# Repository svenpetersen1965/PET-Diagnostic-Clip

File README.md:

# PET-Diagnostic-Clip
This is a modern remake of the two Commodore Diagnostic Clips

<br>Complete Diagnostic Clip Set

<br>Diagnostic Clip installed in a CBM3016 (non CRTC machine)

<br>Diagnostic Clip installed in a CBM8032 (CRTC machine)

# PET Diagnostic Software (40 column, non CRTC):<br>
<br>Opening Screen

<br>Actual tests

<br>Actual tests (continued)

# PET Diagnostic Software (80 column, CRTC):<br>
<br>Opening Screen

<br>Actual tests

# Binaries for the EPROM
The name of the combined file is "80colCRCTv1.1_40colCRCTv2.0_diag3202350g_diag320350g.bin". It contains:
<table>
  <thead>
    <tr>
      <th>EPROM Offset</th><th>Software</th><th>DIP Switch</th>
    </tr>
  </thead>
  <tbody>
    <tr>
      <td>$0000</td><td>80_col_diagnostic_v1.1.bin</td><td>A[15..12]: 0000 =  ON  ON  ON  ON</td>
    </tr>
    <tr>
      <td>$1000</td><td>40_col_diagnostic_v2.0.bin</td><td>A[15..12]: 0001 =  ON  ON  ON  OFF</td>
    </tr>
    <tr>
      <td>$2000</td><td>901447-30_diagnostic_320350g_$9000.bin</td><td>A[15..12]: 0010 =  ON  ON  OFF ON</td>
    </tr>
    <tr>
      <td>$3000</td><td>901447-30_diagnostic_320350g_$9000.bin</td><td>A[15..12]: 0011 =  ON  ON  OFF OFF</td>
    </tr>
 </tbody>
</table>    
    
The Diagnostic 320350g is double. The reason is, the computer would crash if an empty slot is selected. So all slots, that can be selected with the two low switches of the dip switch are occupied.

In a subdirectory, there are some "PETtester" Softwares. These are not a complete test. The (vice) screen shots are included. It could also be installed on the clip, if desired. 
# CBM8296
This part of the project is not tested yet. <b>The release is preliminary</b>.

<br>CBM8296 Diagnostic Harness (complete)

The diagnostic software for the CBM8296 is contained in the respective folder. There is also a merged binary file ("80colCRCTv1.1_40colCRCTv2.0_diag3202350g_diag320350g_8296.bin") which contains the 324806-01.bin at offset address $4000 (A[15..12]: 0100 =  ON  OFF  ON ON).

<b>State of testing:</b><br>
14.06.2023:<br>
* all dongles work with the original (Commodore) clip
* the cassette dongle case reqires modification
21.06.2023:<br>
The CBM8296 can actively switch the /NOROM signal (register @$FFF0). It does so to access the RAM underneath the ROMs. As a result, the diagnostic ROM in the clip is getting visible, which interferes with the test of the upper RAM banks.

A solution is switching off the /NOROM signal in the clip by using the 2nd stage of the external switch. The /NOROM trace at J1, pin 9 has to be cut open and connected to the middle pin of the said switch, the right pin ("active" position) has to be connected to the clip's internal /NOROM signal, e.g. at SW4.  

<br>/NOROM modification of Clip Rev. 2

The clip Rev. 3 incorporates this modificaltion. Since I do not own a CBM8296, I cannot test the new clip with this computer. 

# Additional Information
I have held a presentation about this topic for Commodore Users Europe on Sept. 23rd, 2023. The pdf of the power point presentation can be found here: <a href="https://github.com/svenpetersen1965/PET-Diagnostic-Clip/commit/a3cc22ed0ae75f65ffd660c29feb877c46cf6521">here</a>

Also check my website for <a href="http://tech.guitarsite.de/petcbm_diag_clip.html">additional information</a>.

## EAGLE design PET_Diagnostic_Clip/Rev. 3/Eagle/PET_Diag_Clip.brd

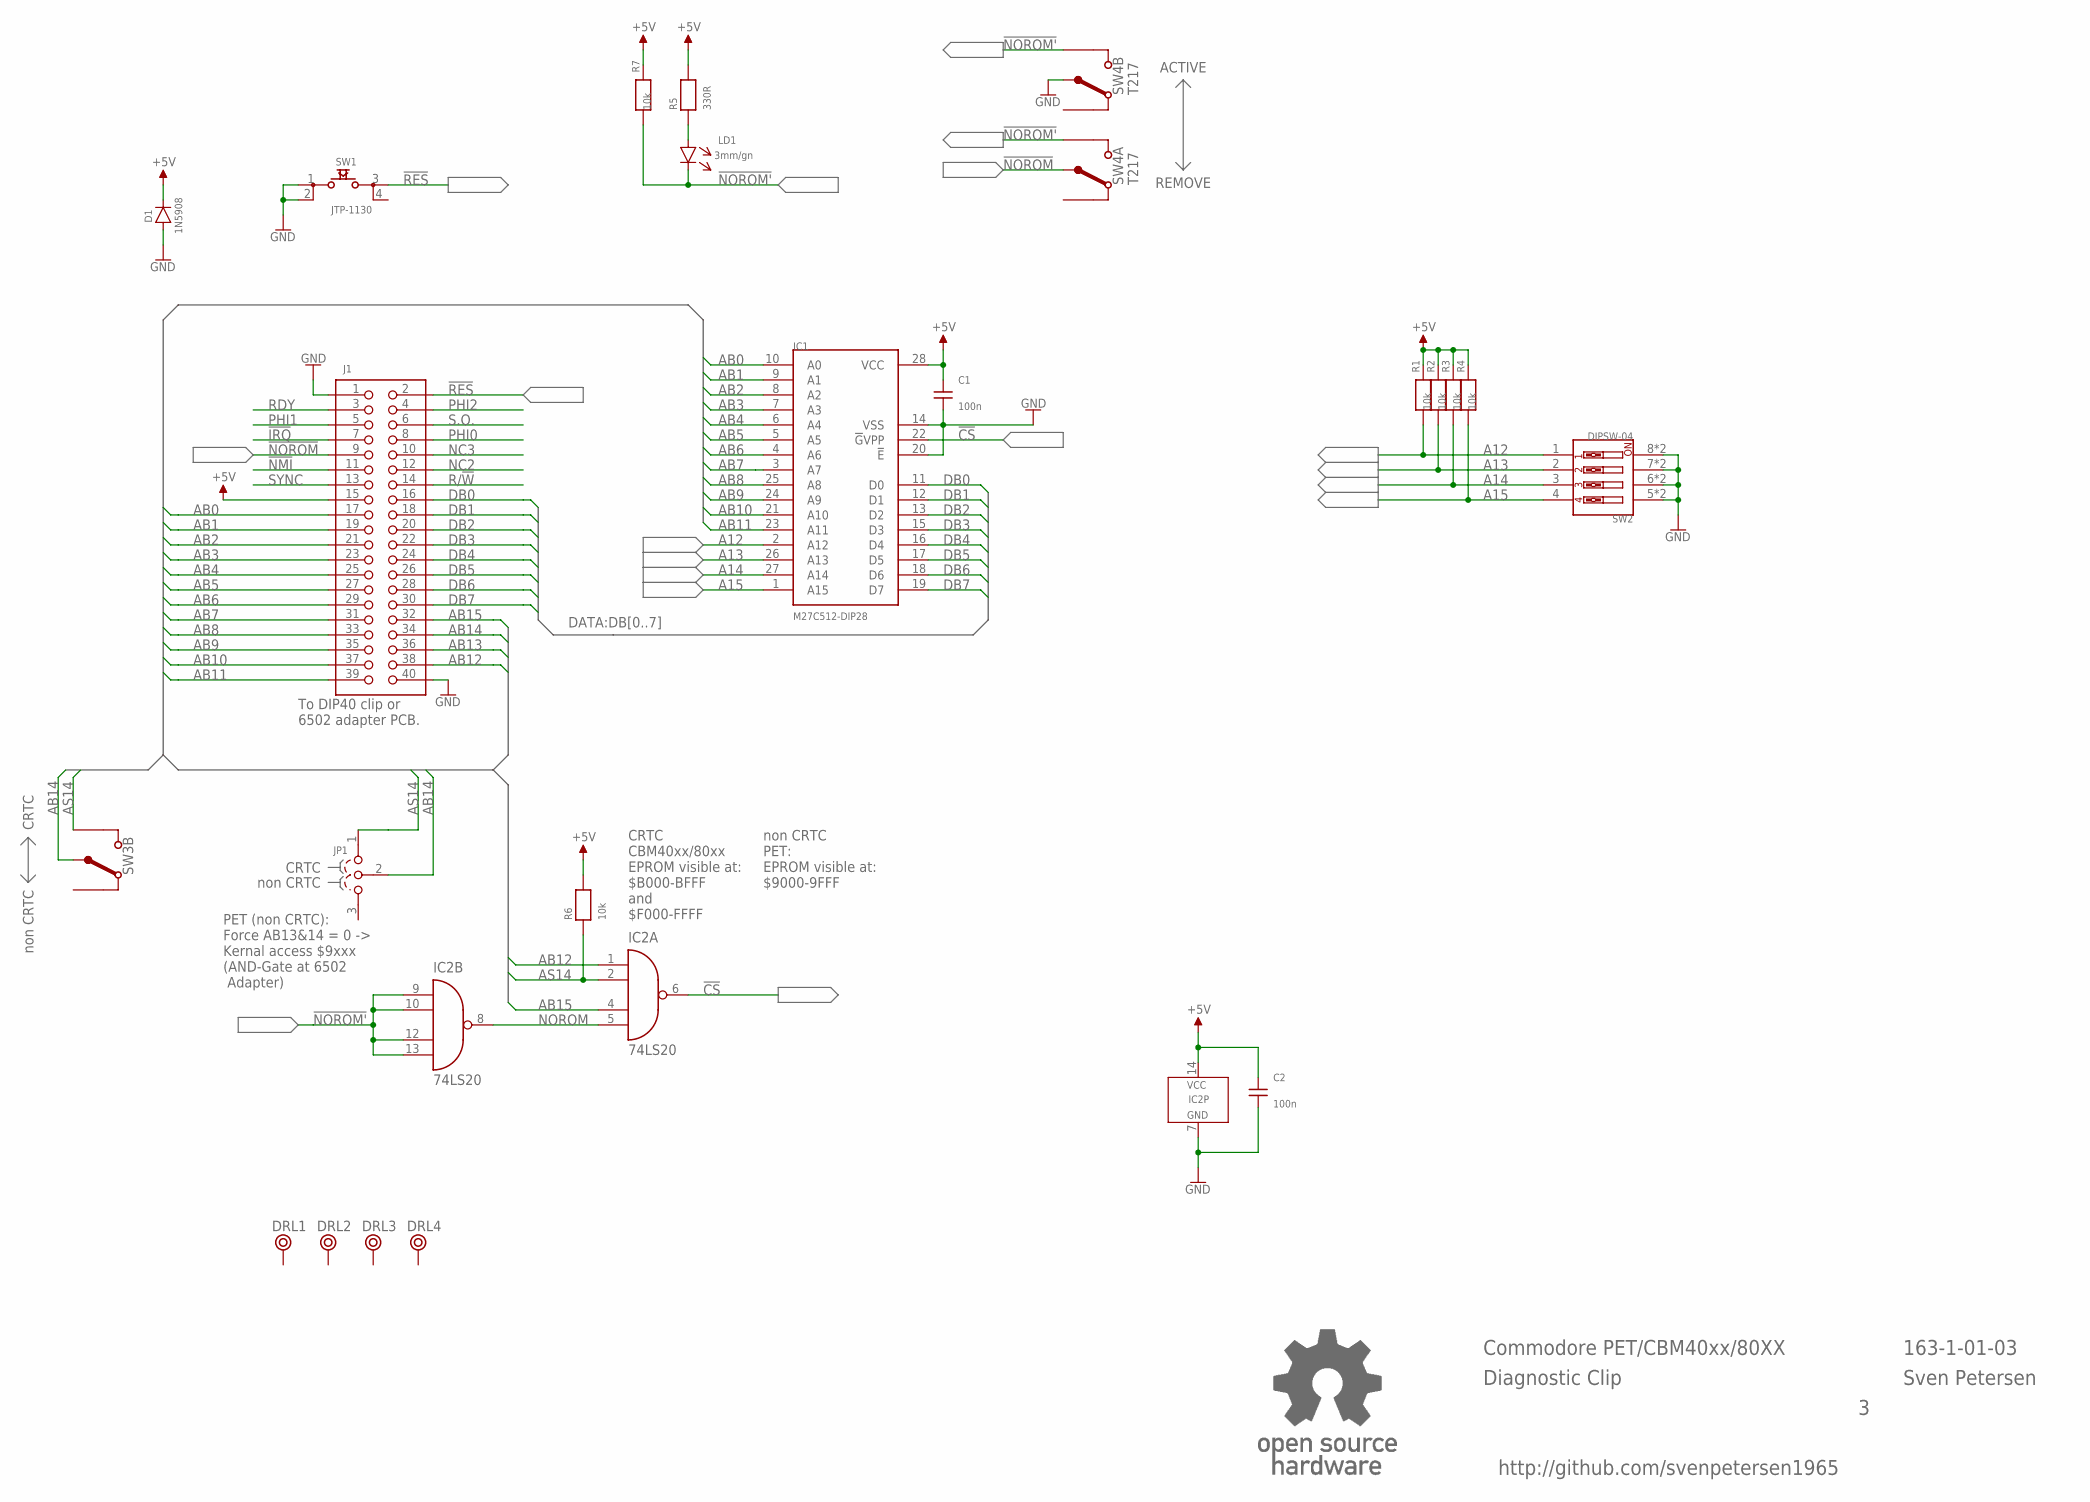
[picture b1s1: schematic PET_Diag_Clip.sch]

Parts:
C1, C2: 100n; C-2,5
D1: 1N5908; DO-201
DRL1, DRL2, DRL3, DRL4: BOHR3,5
IC1: M27C512-DIP28; DIL28-6
IC2: 74LS20; DIL-14
J1: PINHD-2X20WV; 2X20WV
JP1: COMBI-3P
LD1: 3mm/gn; 3MM
R1, R2, R3, R4, R6, R7: 10k; R-10
R5: 330R; R-10
SW1: JTP-1130
SW2: DIPSW-04; DIPSW-04V-COMBI
SW3: MSS22D18; DPDT_9MM
SW4: T217; T217_SIDE
U$13: OPEN_SOURCE_HW; OPENHW

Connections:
!CS: IC1.22 (!G!VPP), IC2.6 (O)
!IRQ: J1.7
!NMI: J1.11
!NOROM: J1.9, SW4.COM1 (COM)
!NOROM': IC2.9 (I0), IC2.10 (I1), IC2.12 (I2), IC2.13 (I3), LD1.C (K), R7.2, SW4.UP1 (UP), SW4.UP2 (UP)
!RES: J1.2, SW1.3
+5V: C1.2, C2.2, D1.K, IC1.28 (VCC), IC2.14 (VCC), J1.15, R1.1, R2.1, R3.1, R4.1, R5.2, R6.2, R7.1
A12: IC1.2 (A12), R1.2, SW2.1
A13: IC1.26 (A13), R2.2, SW2.2
A14: IC1.27 (A14), R3.2, SW2.3
A15: IC1.1 (A15), R4.2, SW2.4
AB0: IC1.10 (A0), J1.17
AB1: IC1.9 (A1), J1.19
AB2: IC1.8 (A2), J1.21
AB3: IC1.7 (A3), J1.23
AB4: IC1.6 (A4), J1.25
AB5: IC1.5 (A5), J1.27
AB6: IC1.4 (A6), J1.29
AB7: IC1.3 (A7), J1.31
AB8: IC1.25 (A8), J1.33
AB9: IC1.24 (A9), J1.35
AB10: IC1.21 (A10), J1.37
AB11: IC1.23 (A11), J1.39
AB12: IC2.1 (I0), J1.38
AB13: J1.36
AB14: J1.34, JP1.2, SW3.5 (COM)
AB15: IC2.4 (I2), J1.32
AS14: IC2.2 (I1), JP1.1, R6.1, SW3.6 (UP)
DB0: IC1.11 (D0), J1.16
DB1: IC1.12 (D1), J1.18
DB2: IC1.13 (D2), J1.20
DB3: IC1.15 (D3), J1.22
DB4: IC1.16 (D4), J1.24
DB5: IC1.17 (D5), J1.26
DB6: IC1.18 (D6), J1.28
DB7: IC1.19 (D7), J1.30
GND: C1.1, C2.1, D1.A, IC1.14 (VSS), IC1.20 (!E), IC2.7 (GND), J1.1, J1.40, SW1.1, SW1.2, SW2.5, SW2.5A (5), SW2.6, SW2.6A (6), SW2.7, SW2.7A (7), SW2.8, SW2.8A (8), SW4.COM2 (COM)
unnamed: LD1.A, R5.1
NC2: J1.12
NC3: J1.10
NOROM: IC2.5 (I3), IC2.8 (O)
PHI0: J1.8
PHI1: J1.5
PHI2: J1.4
R/!W: J1.14
RDY: J1.3
S.O.: J1.6
SYNC: J1.13

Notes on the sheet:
Commodore PET/CBM40xx/80XX
Diagnostic Clip
Sven Petersen
163-1-01-03
http://github.com/svenpetersen1965
To DIP40 clip or 6502 adapter PCB.
CRTC CBM40xx/80xx EPROM visible at: $B000-BFFF and $F000-FFFF
CRTC
non CRTC
PET (non CRTC): Force AB13&14 = 0 -> Kernal access $9xxx (AND-Gate at 6502 Adapter)
non CRTC PET: EPROM visible at: $9000-9FFF
ACTIVE
REMOVE

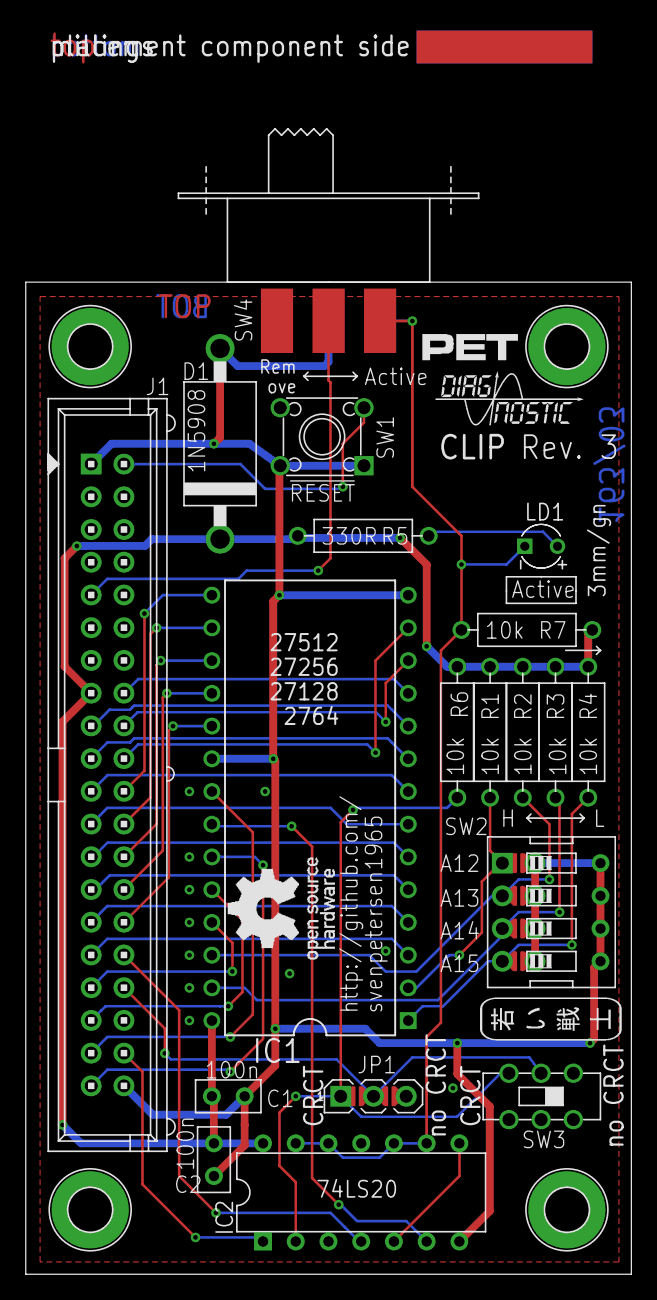
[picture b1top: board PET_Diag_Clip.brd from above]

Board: 2 copper layers, 47.0 x 77.0 mm, 29 parts (0 on the bottom side), 36 nets.

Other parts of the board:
U$27: PET_SMALL
U$30: DIAG_SMALL
U$34: 2LAYER
U$35: PCB-TITLE/
U$42: SVEN_TAG

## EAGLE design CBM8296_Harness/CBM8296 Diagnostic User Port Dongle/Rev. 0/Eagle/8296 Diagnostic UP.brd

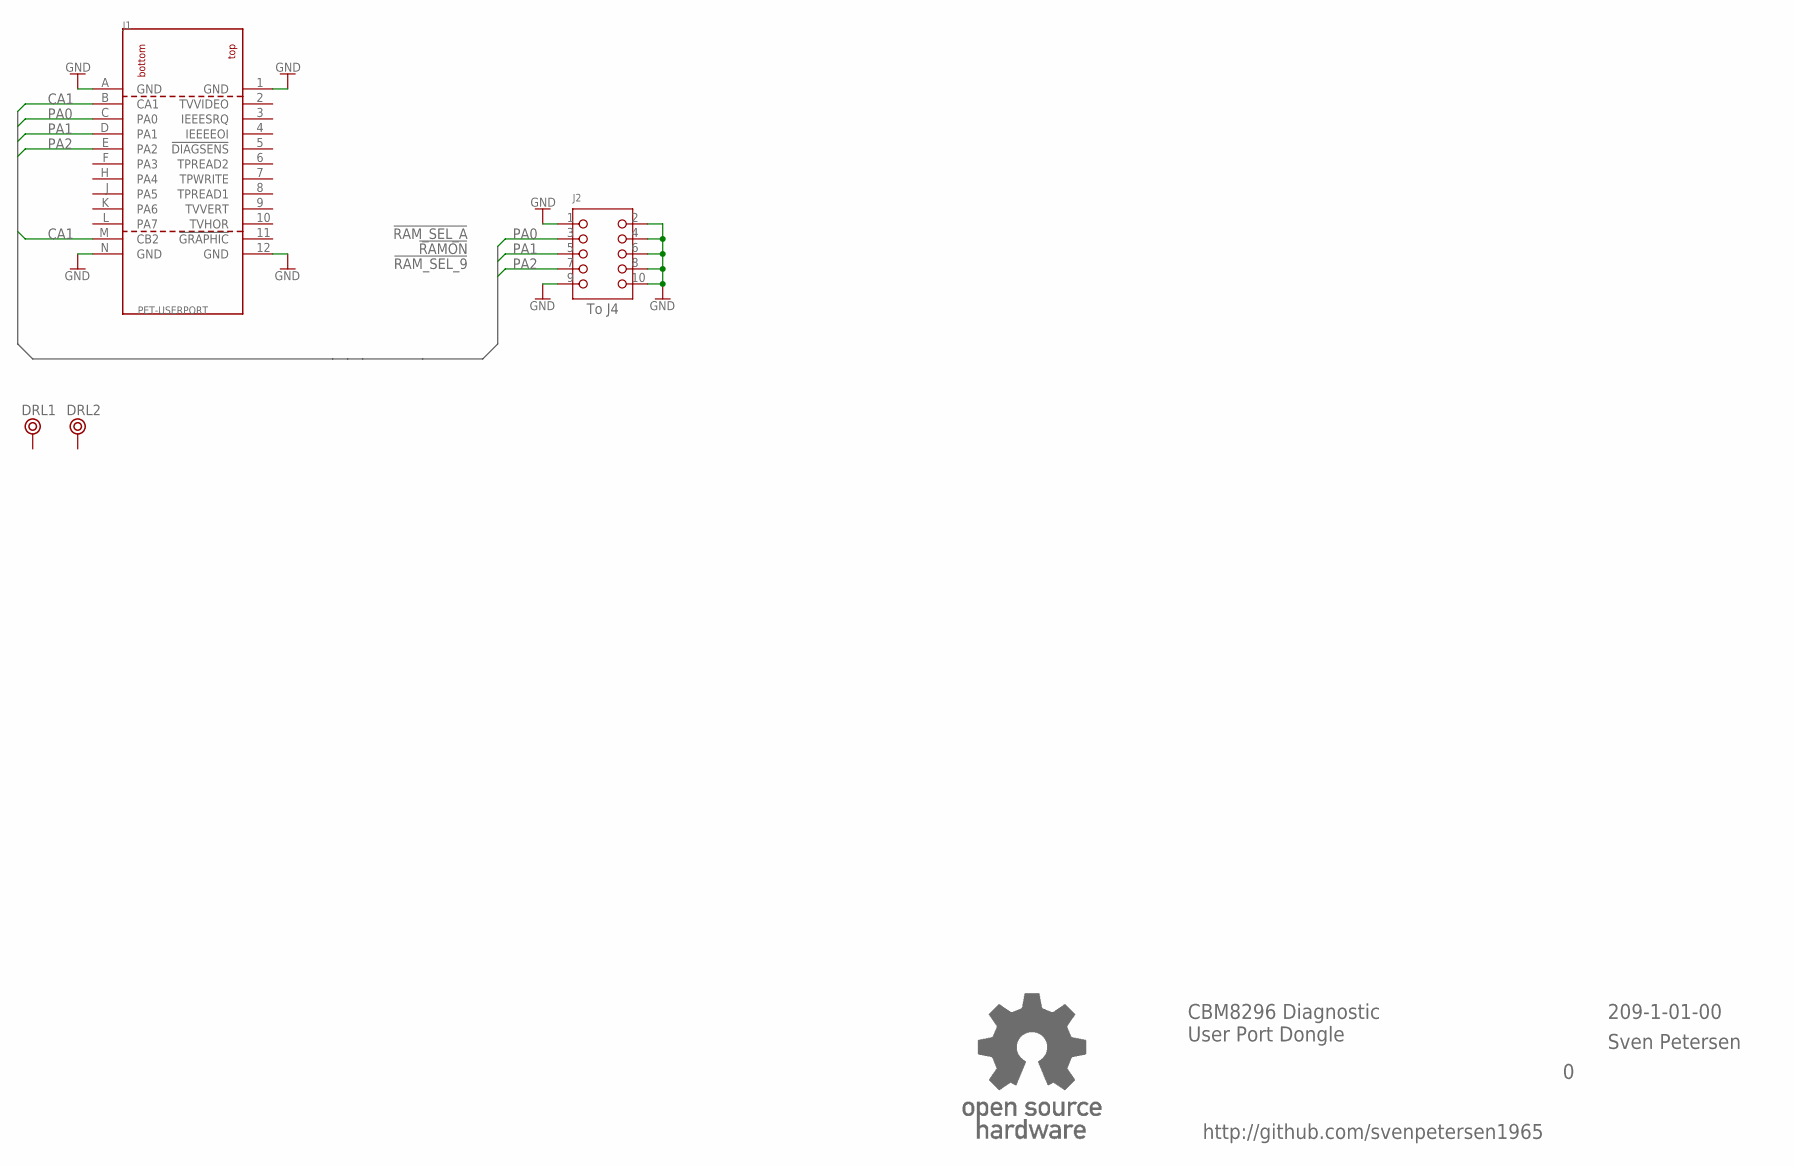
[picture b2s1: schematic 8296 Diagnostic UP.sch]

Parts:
DRL1, DRL2: BOHR3,5
J1: PET-USERPORT; USERPORT
J2: 2X05WV
U$13: OPEN_SOURCE_HW; OPENHW

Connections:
CA1: J1.B (CA1), J1.M (CB2)
GND: J1.1 (GND), J1.12 (GND), J1.A (GND), J1.N (GND), J2.1, J2.2, J2.4, J2.6, J2.8, J2.9, J2.10
PA0: J1.C (PA0), J2.3
PA1: J1.D (PA1), J2.5
PA2: J1.E (PA2), J2.7

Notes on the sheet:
CBM8296 Diagnostic User Port Dongle
209-1-01-00
Sven Petersen
http://github.com/svenpetersen1965
To J4
!RAM_SEL_A
!RAMON
!RAM_SEL_9

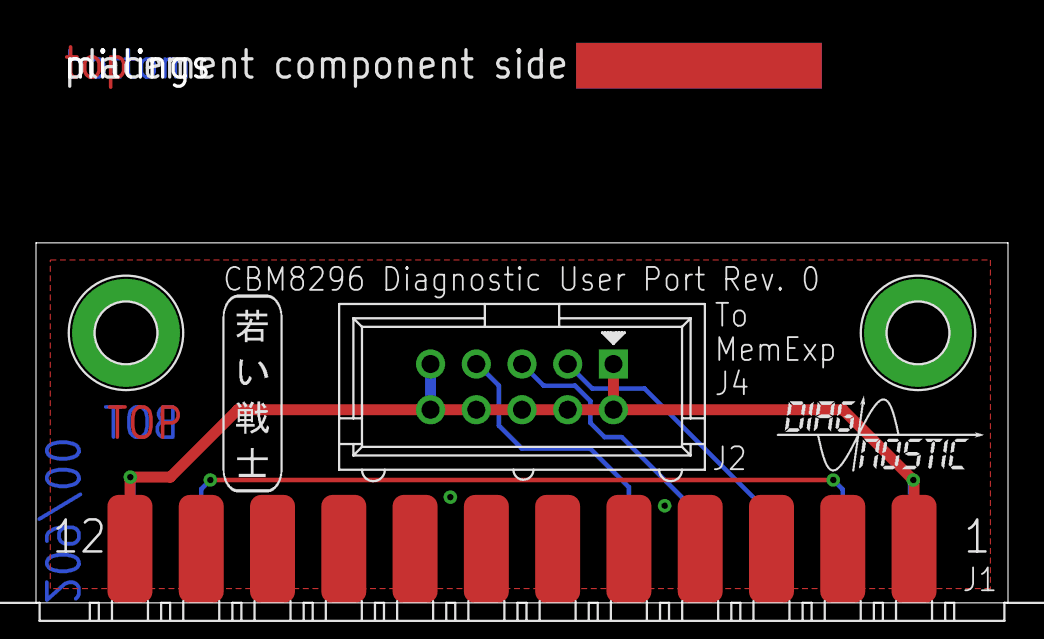
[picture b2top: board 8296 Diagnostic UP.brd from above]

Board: 2 copper layers, 54.0 x 20.0 mm, 9 parts (1 on the bottom side), 5 nets.

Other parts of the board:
U$8: 2LAYER
U$9: PCB-TITLE/
U$10: SVEN_TAG
U$12: DIAG_SMALL

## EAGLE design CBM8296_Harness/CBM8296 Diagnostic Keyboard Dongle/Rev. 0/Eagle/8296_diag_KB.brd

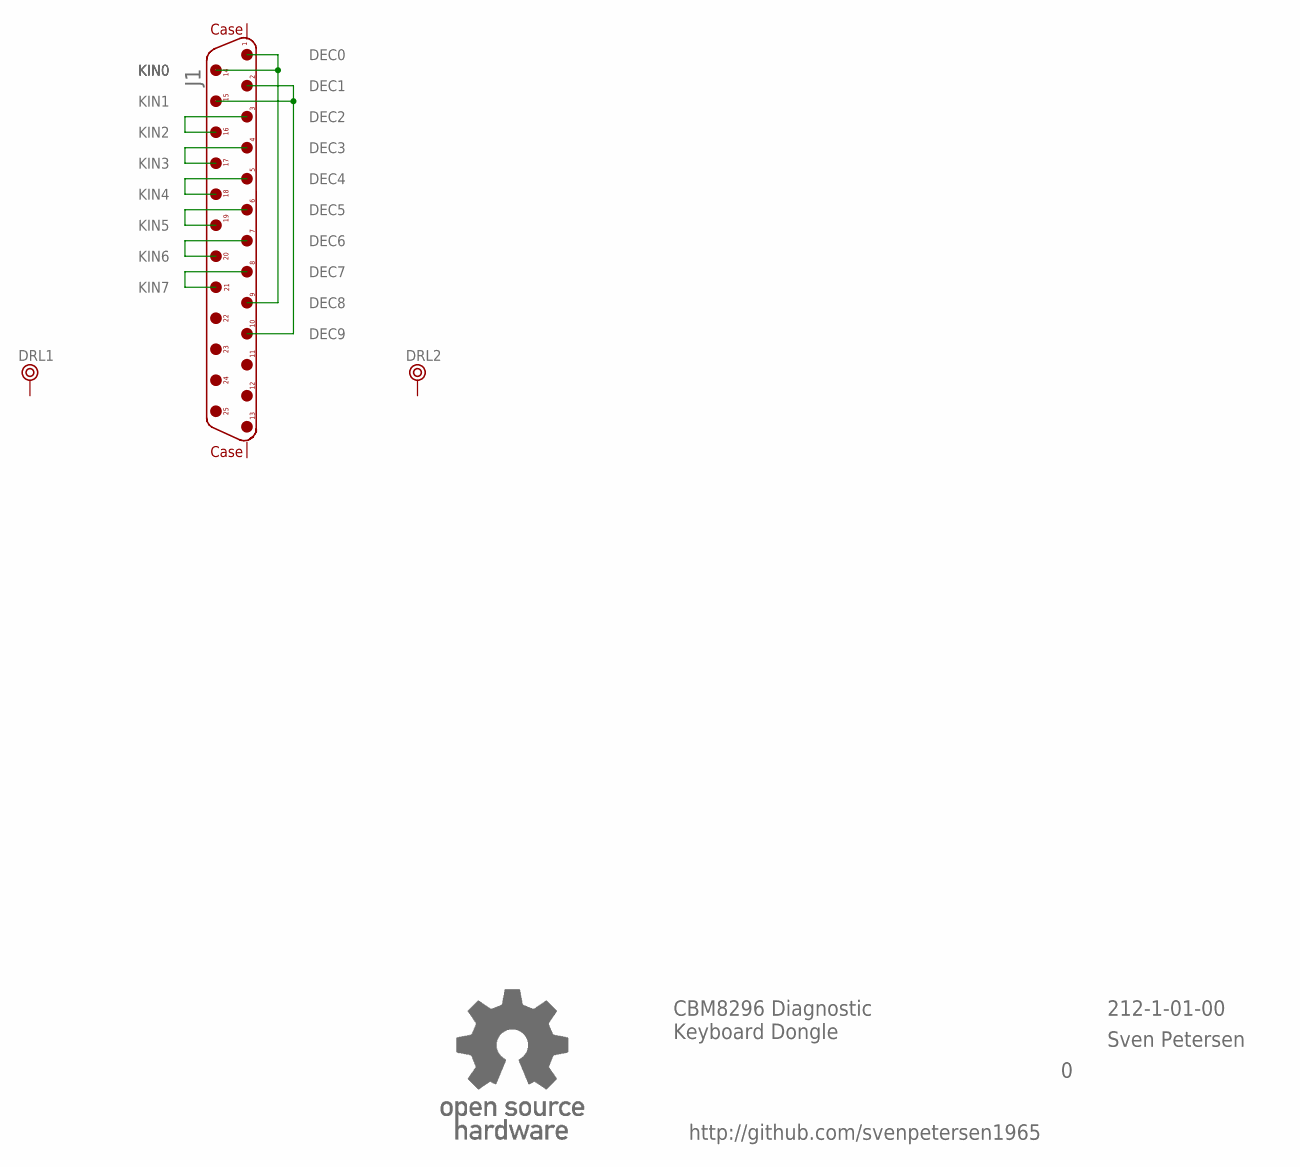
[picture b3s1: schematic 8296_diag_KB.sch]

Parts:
DRL1, DRL2: BOHR3,5
J1: D25M90CLEU
U$13: OPEN_SOURCE_HW; OPENHW

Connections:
unnamed: J1.1, J1.9, J1.14
unnamed: J1.2, J1.10, J1.15
unnamed: J1.3, J1.16
unnamed: J1.4, J1.17
unnamed: J1.5, J1.18
unnamed: J1.6, J1.19
unnamed: J1.7, J1.20
unnamed: J1.8, J1.21

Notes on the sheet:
CBM8296 Diagnostic Keyboard Dongle
212-1-01-00
Sven Petersen
http://github.com/svenpetersen1965
DEC0
DEC1
DEC2
DEC3
DEC4
DEC6
DEC5
DEC7
DEC8
DEC9
KIN0
KIN1
KIN2
KIN3
KIN4
KIN5
KIN6
KIN7

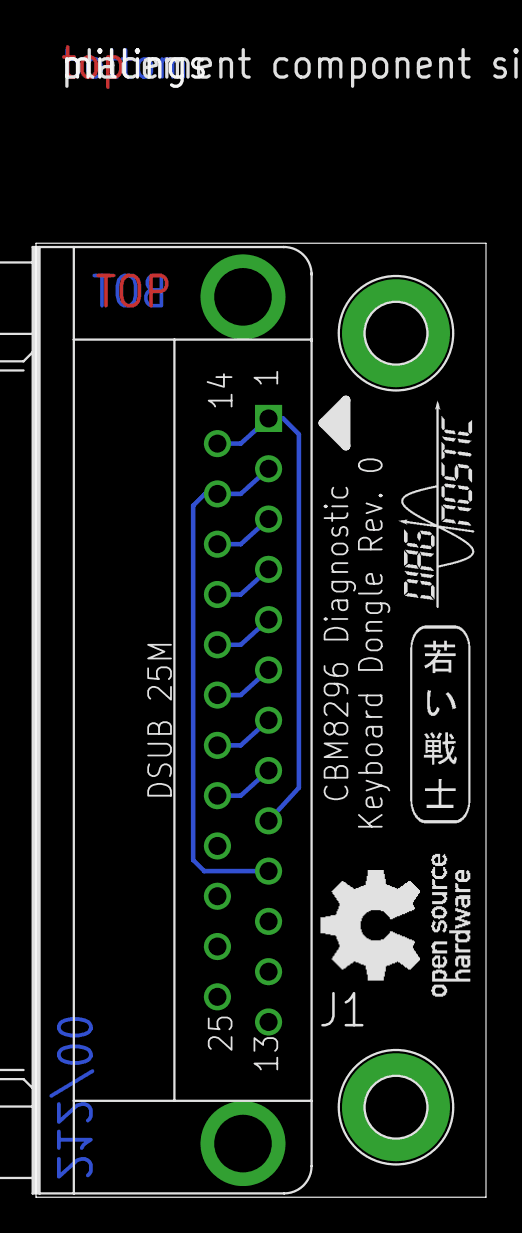
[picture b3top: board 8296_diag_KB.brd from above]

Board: 2 copper layers, 25.0 x 53.0 mm, 8 parts (0 on the bottom side), 8 nets.

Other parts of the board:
U$2: DIAG_SMALL
U$3: SVEN_TAG
U$4: 2LAYER
U$5: PCB-TITLE/

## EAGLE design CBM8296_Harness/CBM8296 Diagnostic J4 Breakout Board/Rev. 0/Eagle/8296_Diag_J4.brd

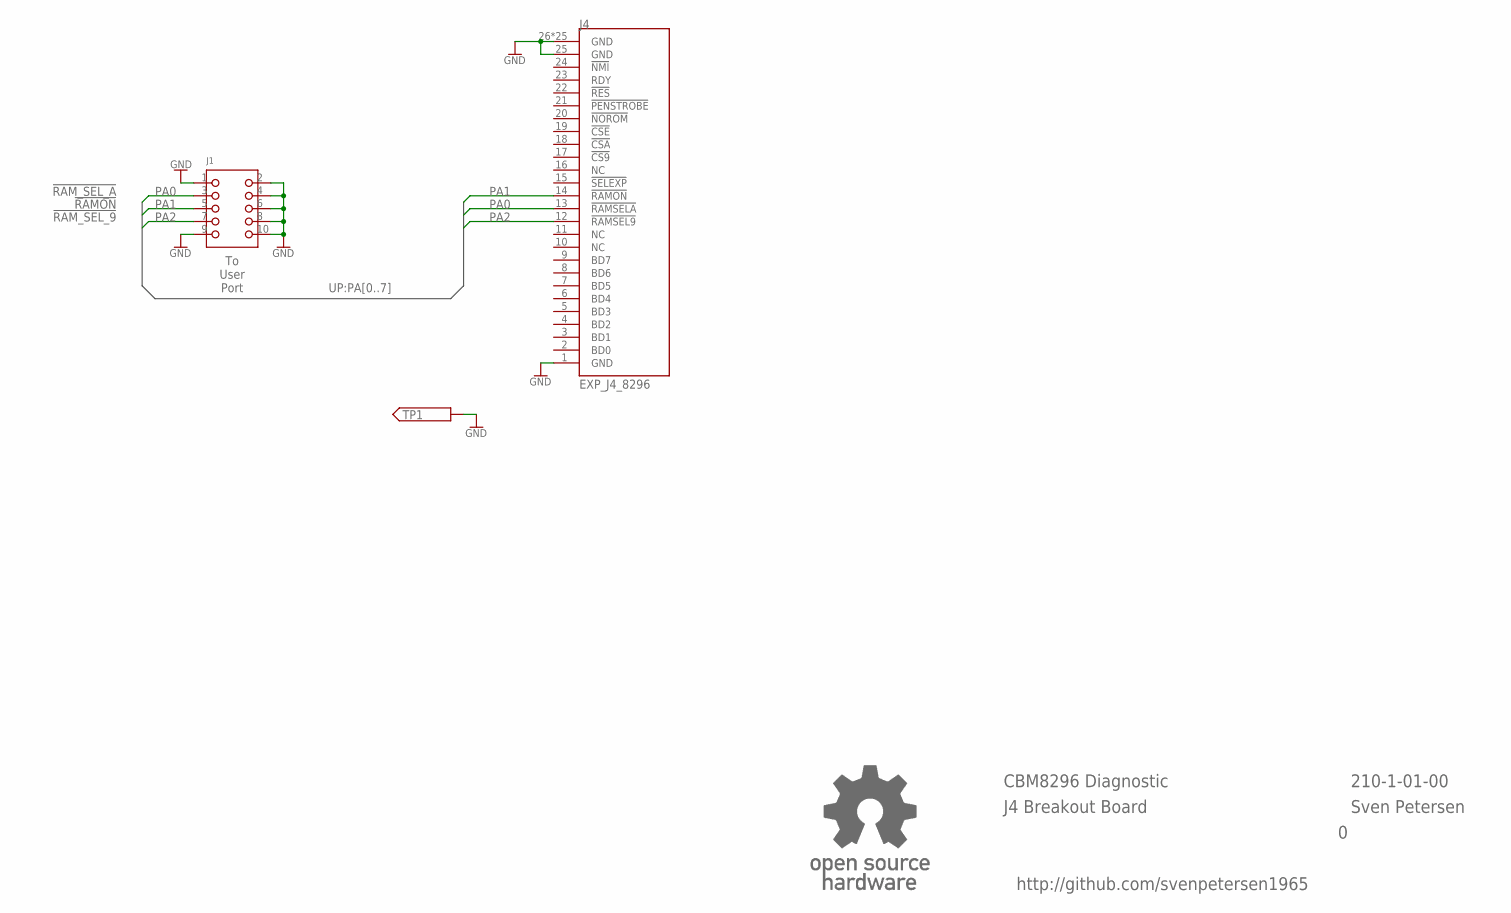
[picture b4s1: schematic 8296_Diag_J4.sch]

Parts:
J1: 2X05WV
J4: EXP_J4_8296; PET_EXPANSION_BOT
TP1: PINHD-1X1; 1X01
U$5: OPEN_SOURCE_HW; OPENHW

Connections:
GND: J1.1, J1.2, J1.4, J1.6, J1.8, J1.9, J1.10, J4.1 (GND), J4.25 (GND), J4.26 (GND), J4.27 (GND), J4.28 (GND), J4.29 (GND), J4.30 (GND), J4.31 (GND), J4.32 (GND), J4.33 (GND), J4.34 (GND), J4.35 (GND), J4.36 (GND), J4.37 (GND), J4.38 (GND), J4.39 (GND), J4.40 (GND), J4.41 (GND), J4.42 (GND), J4.43 (GND), J4.44 (GND), J4.45 (GND), J4.46 (GND), J4.47 (GND), J4.48 (GND), J4.49 (GND), J4.50 (GND), TP1.1
PA0: J1.3, J4.13 (!RAMSELA)
PA1: J1.5, J4.14 (!RAMON)
PA2: J1.7, J4.12 (!RAMSEL9)

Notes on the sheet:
CBM8296 Diagnostic
J4 Breakout Board
210-1-01-00
Sven Petersen
http://github.com/svenpetersen1965
To User Port
!RAM_SEL_A
!RAMON
!RAM_SEL_9

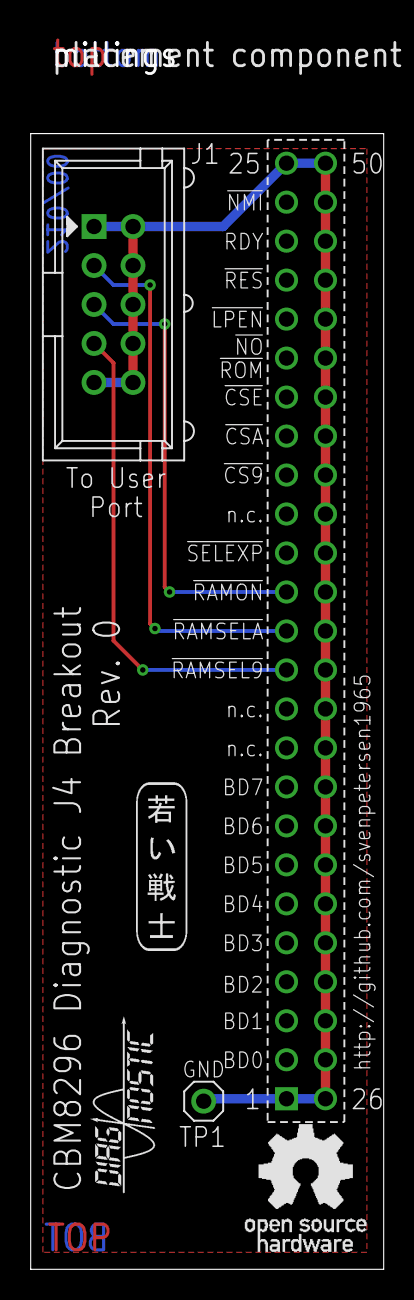
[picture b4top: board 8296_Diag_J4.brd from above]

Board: 2 copper layers, 23.0 x 74.0 mm, 8 parts (0 on the bottom side), 4 nets.

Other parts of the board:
U$8: 2LAYER
U$9: SVEN_TAG
U$10: PCB-TITLE/
U$12: DIAG_SMALL

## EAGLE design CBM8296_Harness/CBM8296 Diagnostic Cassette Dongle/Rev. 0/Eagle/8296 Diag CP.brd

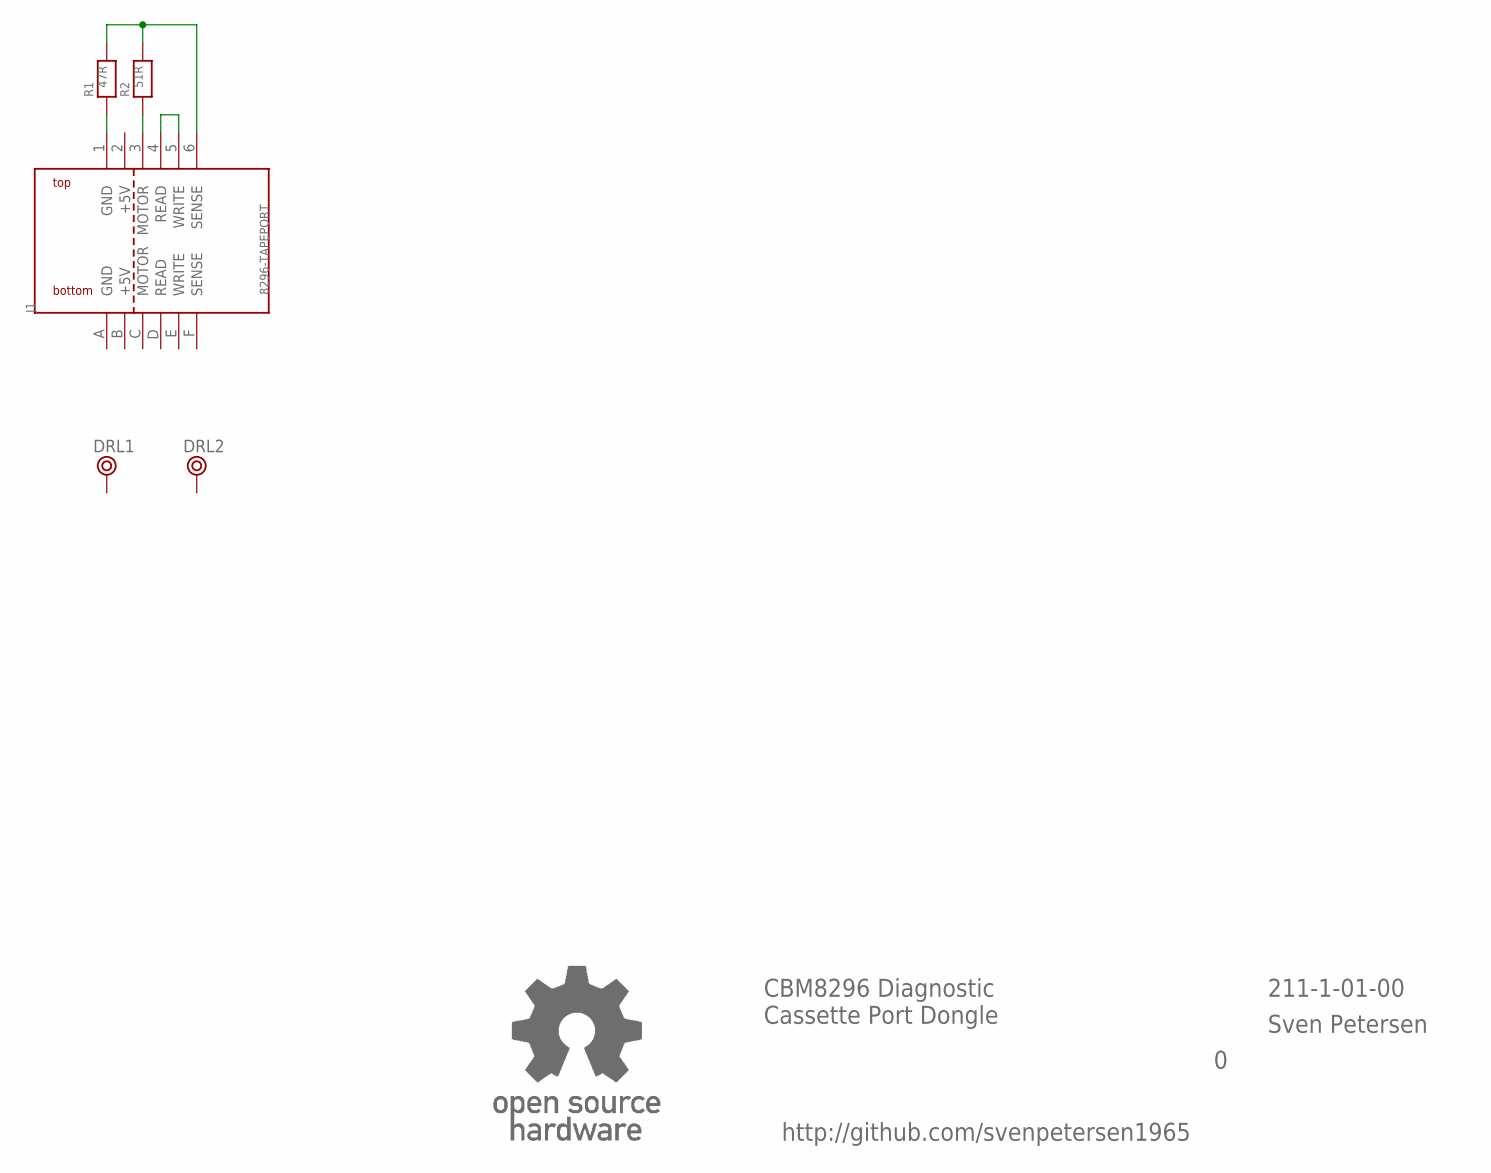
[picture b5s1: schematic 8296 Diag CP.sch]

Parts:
DRL1, DRL2: BOHR3,5
J1: 8296-TAPEPORT; TAPEPORT
R1: 47R; R-10
R2: 51R; R-10
U$13: OPEN_SOURCE_HW; OPENHW

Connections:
+5V: J1.2 (+5V), J1.B (+5V)
GND: J1.A (GND)
unnamed: J1.6 (SENSE), R1.2, R2.2
unnamed: J1.3 (MOTOR), R2.1
unnamed: J1.1 (GND), R1.1
unnamed: J1.4 (READ), J1.5 (WRITE)

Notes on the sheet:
CBM8296 Diagnostic Cassette Port Dongle
211-1-01-00
Sven Petersen
http://github.com/svenpetersen1965

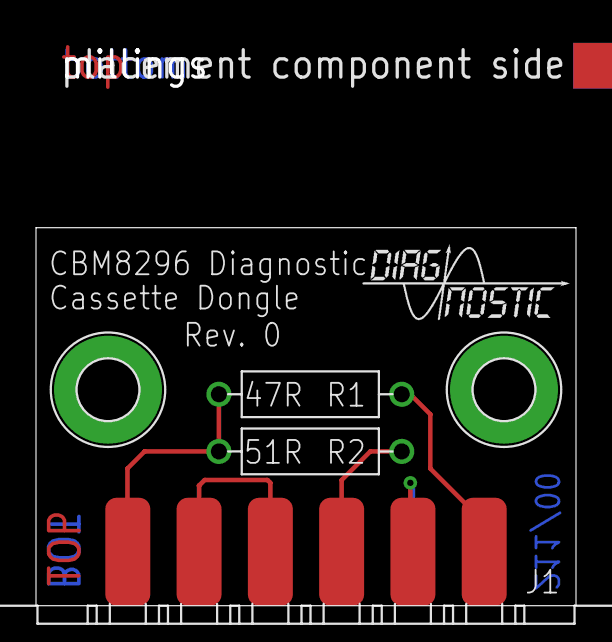
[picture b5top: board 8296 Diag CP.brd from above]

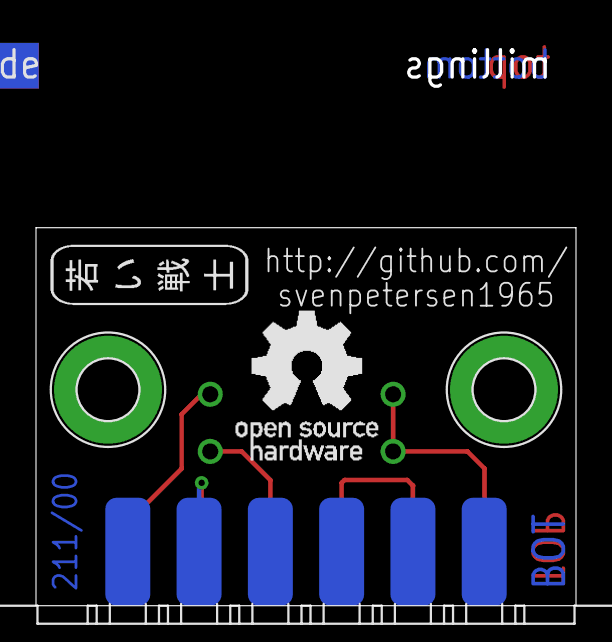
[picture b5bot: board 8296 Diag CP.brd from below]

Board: 2 copper layers, 30.0 x 21.0 mm, 10 parts (2 on the bottom side), 5 nets.

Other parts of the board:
U$2: DIAG_SMALL
U$3: 2LAYER
U$4: SVEN_TAG
U$5: PCB-TITLE/

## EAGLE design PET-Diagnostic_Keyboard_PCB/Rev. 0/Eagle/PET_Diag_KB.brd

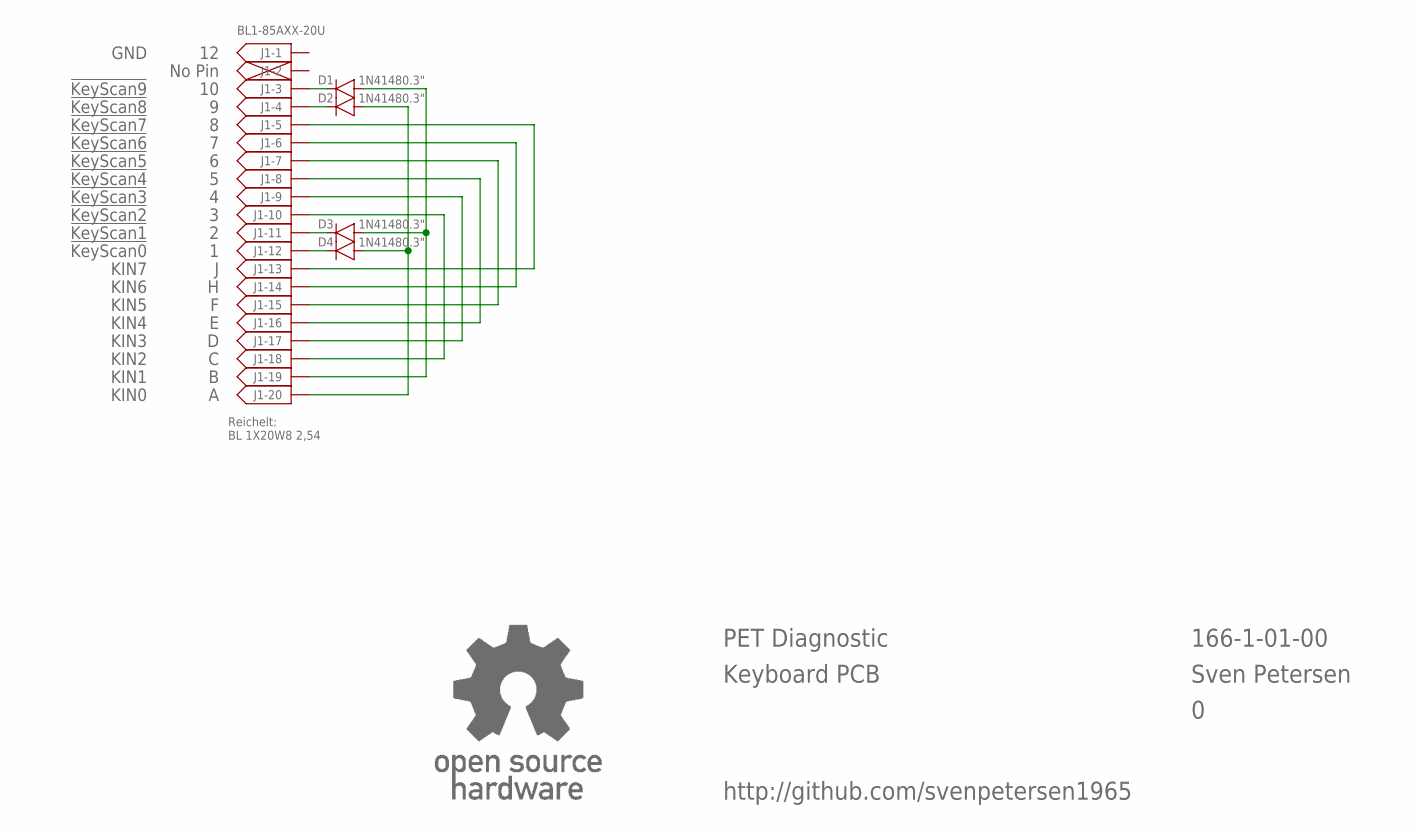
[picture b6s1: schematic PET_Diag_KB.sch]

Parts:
D1, D2, D3, D4: 1N41480.3"; DO-35/3
J1: BL1-85AXX-20U
U$9: OPEN_SOURCE_HW; OPENHW

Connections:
unnamed: D1.K, J1.3
unnamed: D2.A, D4.A, J1.20
unnamed: D1.A, D3.A, J1.19
unnamed: J1.10, J1.18
unnamed: J1.9, J1.17
unnamed: J1.8, J1.16
unnamed: J1.7, J1.15
unnamed: J1.6, J1.14
unnamed: J1.5, J1.13
unnamed: D2.K, J1.4
unnamed: D3.K, J1.11
unnamed: D4.K, J1.12

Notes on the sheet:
No Pin
PET Diagnostic
Keyboard PCB
166-1-01-00
Sven Petersen
Reichelt: BL 1X20W8 2,54
http://github.com/svenpetersen1965
!KeyScan0
!KeyScan1
!KeyScan2
!KeyScan3
!KeyScan4
!KeyScan5
!KeyScan6
!KeyScan7
!KeyScan8
!KeyScan9
KIN0
KIN1
KIN2
KIN3
KIN4
KIN5
KIN6
KIN7
GND

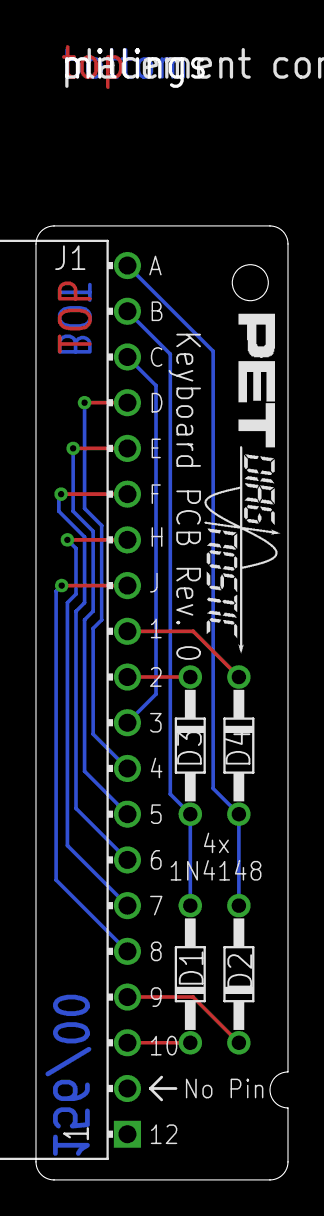
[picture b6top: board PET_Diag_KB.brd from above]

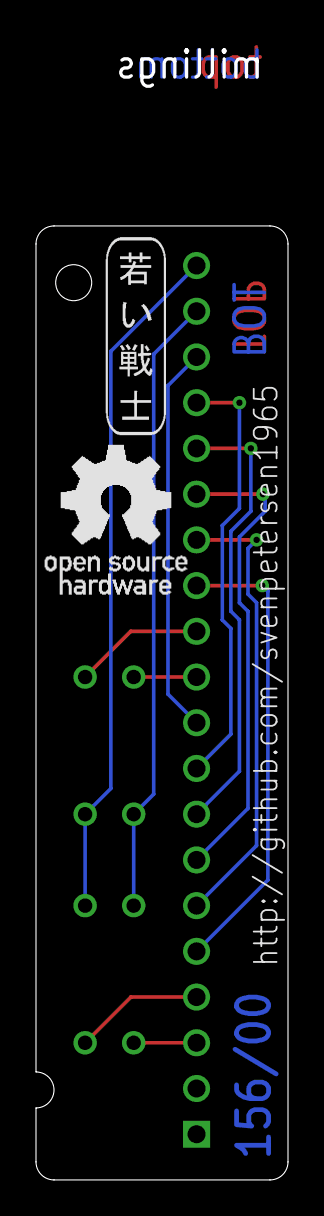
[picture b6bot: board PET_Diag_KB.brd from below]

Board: 2 copper layers, 14.0 x 53.0 mm, 11 parts (2 on the bottom side), 12 nets.

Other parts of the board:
U$2: DIAG_SMALL
U$3: PET_SMALL
U$6: 2LAYER
U$7: PCB-TITLE/
U$8: SVEN_TAG

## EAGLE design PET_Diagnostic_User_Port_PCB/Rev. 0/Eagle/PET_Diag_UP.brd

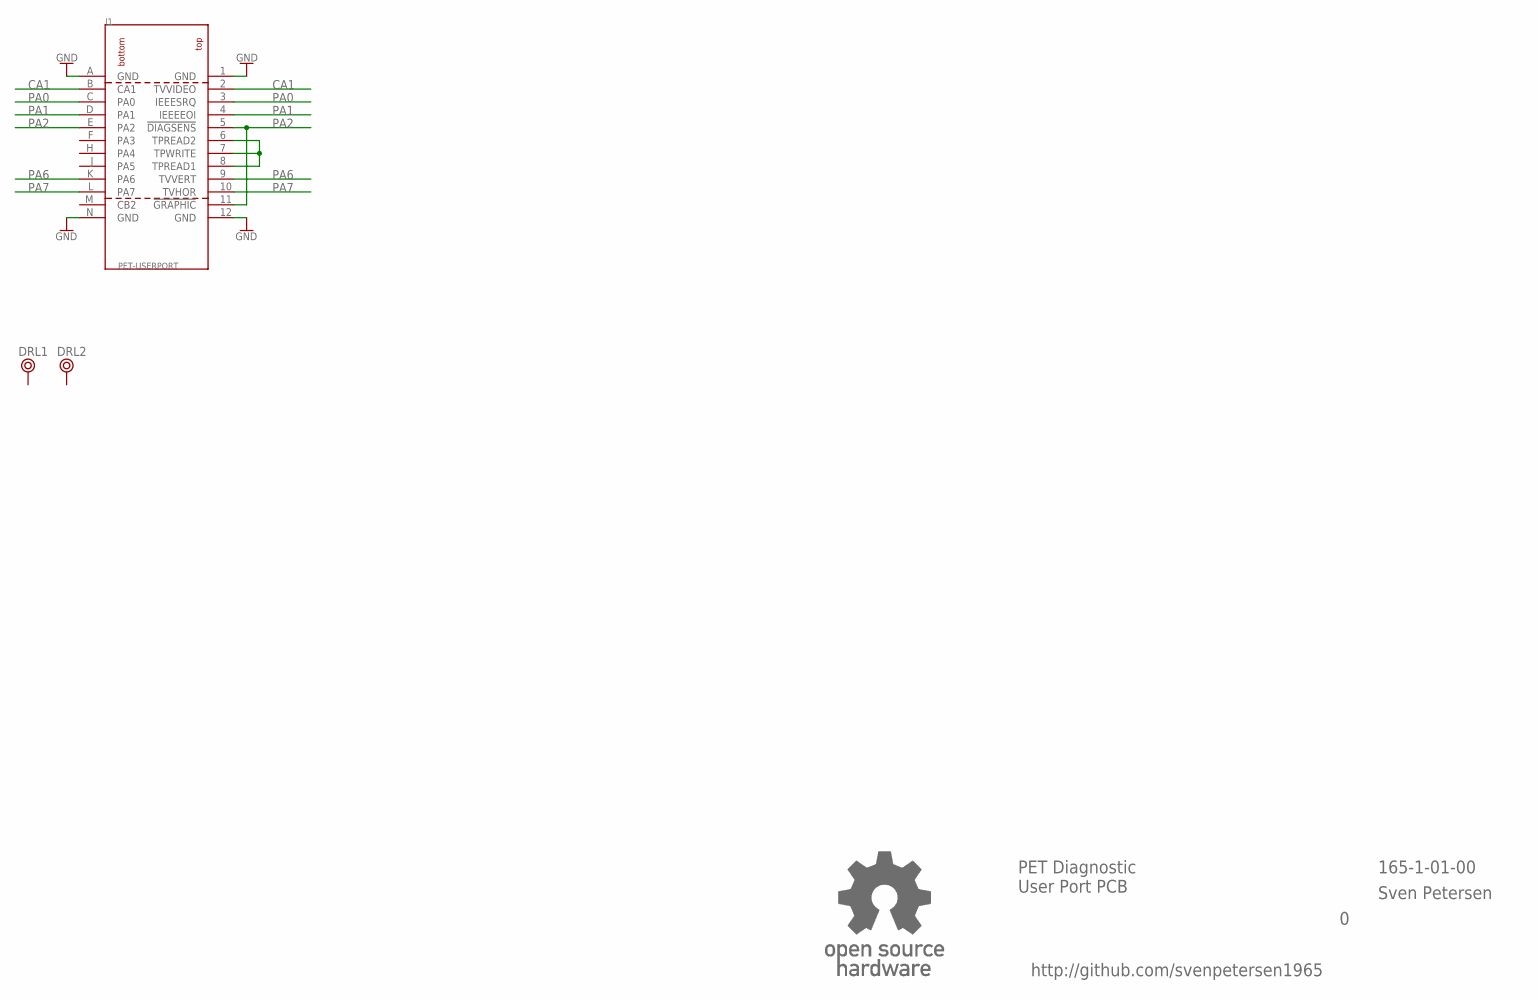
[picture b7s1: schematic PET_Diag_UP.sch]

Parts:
DRL1, DRL2: BOHR3,5
J1: PET-USERPORT; USERPORT
U$13: OPEN_SOURCE_HW; OPENHW

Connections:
CA1: J1.2 (TVVIDEO), J1.B (CA1)
GND: J1.1 (GND), J1.12 (GND), J1.A (GND), J1.N (GND)
unnamed: J1.6 (TPREAD2), J1.7 (TPWRITE), J1.8 (TPREAD1)
PA0: J1.3 (IEEESRQ), J1.C (PA0)
PA1: J1.4 (IEEEEOI), J1.D (PA1)
PA2: J1.5 (!DIAGSENS), J1.11 (!GRAPHIC), J1.E (PA2)
PA6: J1.9 (TVVERT), J1.K (PA6)
PA7: J1.10 (TVHOR), J1.L (PA7)

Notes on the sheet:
PET Diagnostic User Port PCB
165-1-01-00
Sven Petersen
http://github.com/svenpetersen1965

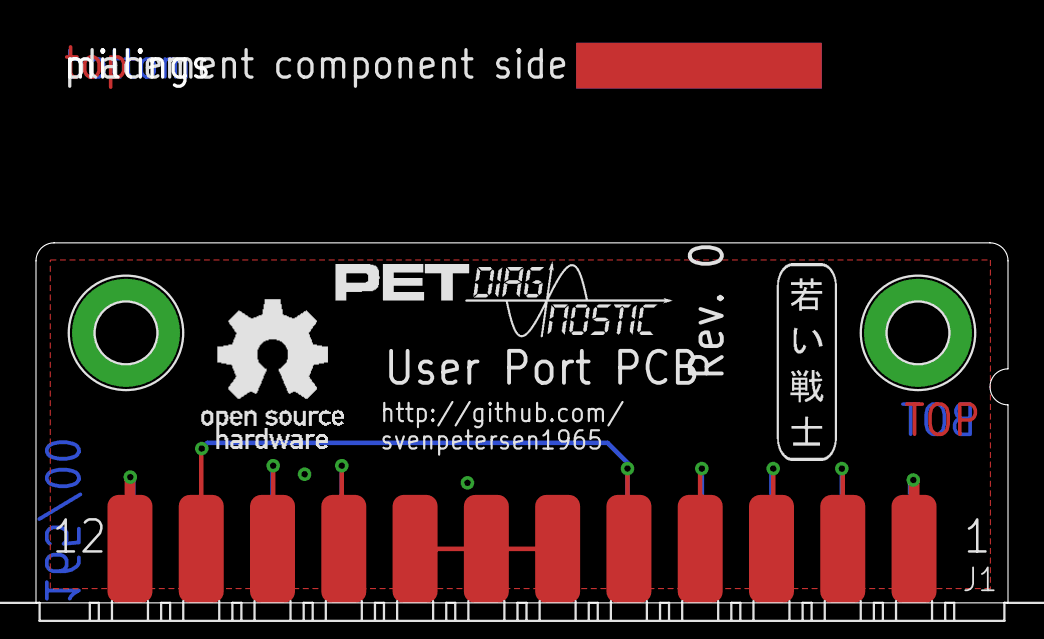
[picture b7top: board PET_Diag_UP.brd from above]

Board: 2 copper layers, 54.0 x 20.0 mm, 9 parts (0 on the bottom side), 8 nets.

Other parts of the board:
U$6: DIAG_SMALL
U$7: PET_SMALL
U$8: 2LAYER
U$9: PCB-TITLE/
U$10: SVEN_TAG
